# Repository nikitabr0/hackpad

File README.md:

# nikitabr0's hackpad

[Demo video](https://youtu.be/7ATBC-yoFk0)

<table>
  <tr>
    <td>
    <td>
  </tr>
  <tr>
    <td>
    <td>
  </tr>
</table>   

My hackpad features 9 MX-style keyswitches and two EC11 rotary encoders. It has two modes: media control and gaming mode, the latter being mostly for simulators, that require large amounts of keybinds.

In media control mode the keys can be used for pausing, resuming and switching between audiotracks, as well as for using the calcuator (+, -, *, / and =), while the rotary encoders allow for audio volume and screen brightness control, with their switches set to muting audio and locking the screen.

In gaming mode all switches (including those of EC11s) register as F13-F22 presses, with the rotary encoders triggering Right CTRL + F13/14/15/16 on rotation. These keycodes were choosed as they are not included on most keyboards and thus largely unused.

The firmware if written in KMK for the sake of simplicity, although I may try rewriting it in QMK one day. The CAD was done in FreeCAD.

#

### Schematic

### PCB layout

### Case assembly

#

## Bill of materials:
- 1x Seeed XIAO RP2040 DIP
- 9x MX-style switches
- 2x EC11 rotary encoders
- 9x Blank DSA keycaps
- 11x Through-hole 1N4148 diodes
- 4x M3x5mx4mm heatset inserts

I will be printing the case by myself and as I already have some mounting hardware, I will be using it in this project:
- 4x M3x12 SHCS
- 3x M3x8 SHCS

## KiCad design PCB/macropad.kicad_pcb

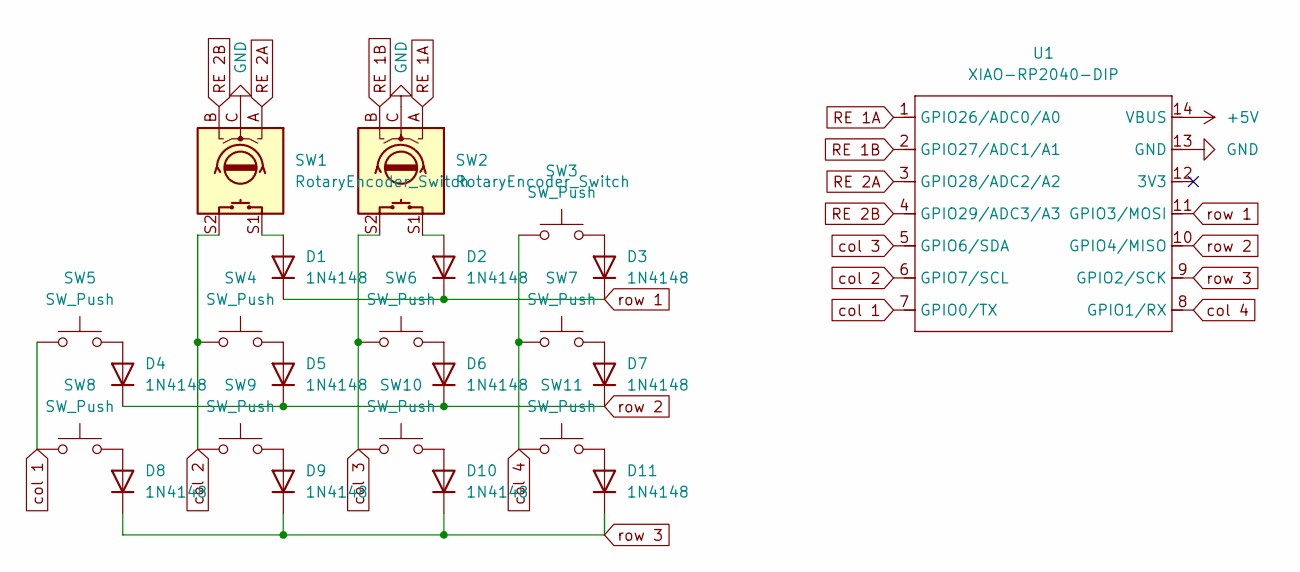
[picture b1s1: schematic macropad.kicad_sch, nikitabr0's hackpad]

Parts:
D1, D2, D3, D4, D5, D6, D7, D8, D9, D10, D11: 1N4148; D_DO-35_SOD27_P7.62mm_Horizontal
SW1, SW2: RotaryEncoder_Switch; RotaryEncoder_Alps_EC11E-Switch_Vertical_H20mm
SW3, SW4, SW5, SW6, SW7, SW8, SW9, SW10, SW11: SW_Push; SW_Cherry_MX_PCB_1.00u
U1: XIAO-RP2040-DIP

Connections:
+5V: U1.14 (VBUS)
GND: SW1.C, SW2.C, U1.13 (GND)
unnamed: D1.2 (A), SW1.S1
unnamed: D2.2 (A), SW2.S1
unnamed: D3.2 (A), SW3.2
unnamed: D4.2 (A), SW5.2
unnamed: D5.2 (A), SW4.2
unnamed: D6.2 (A), SW6.2
unnamed: D7.2 (A), SW7.2
unnamed: D8.2 (A), SW8.2
unnamed: D9.2 (A), SW9.2
unnamed: D10.2 (A), SW10.2
unnamed: D11.2 (A), SW11.2
RE 1A: SW2.A, U1.1 (GPIO26/ADC0/A0)
RE 1B: SW2.B, U1.2 (GPIO27/ADC1/A1)
RE 2A: SW1.A, U1.3 (GPIO28/ADC2/A2)
RE 2B: SW1.B, U1.4 (GPIO29/ADC3/A3)
col 1: SW5.1, SW8.1, U1.7 (GPIO0/TX)
col 2: SW1.S2, SW4.1, SW9.1, U1.6 (GPIO7/SCL)
col 3: SW2.S2, SW6.1, SW10.1, U1.5 (GPIO6/SDA)
col 4: SW3.1, SW7.1, SW11.1, U1.8 (GPIO1/RX)
row 1: D1.1 (K), D2.1 (K), D3.1 (K), U1.11 (GPIO3/MOSI)
row 2: D4.1 (K), D5.1 (K), D6.1 (K), D7.1 (K), U1.10 (GPIO4/MISO)
row 3: D8.1 (K), D9.1 (K), D10.1 (K), D11.1 (K), U1.9 (GPIO2/SCK)

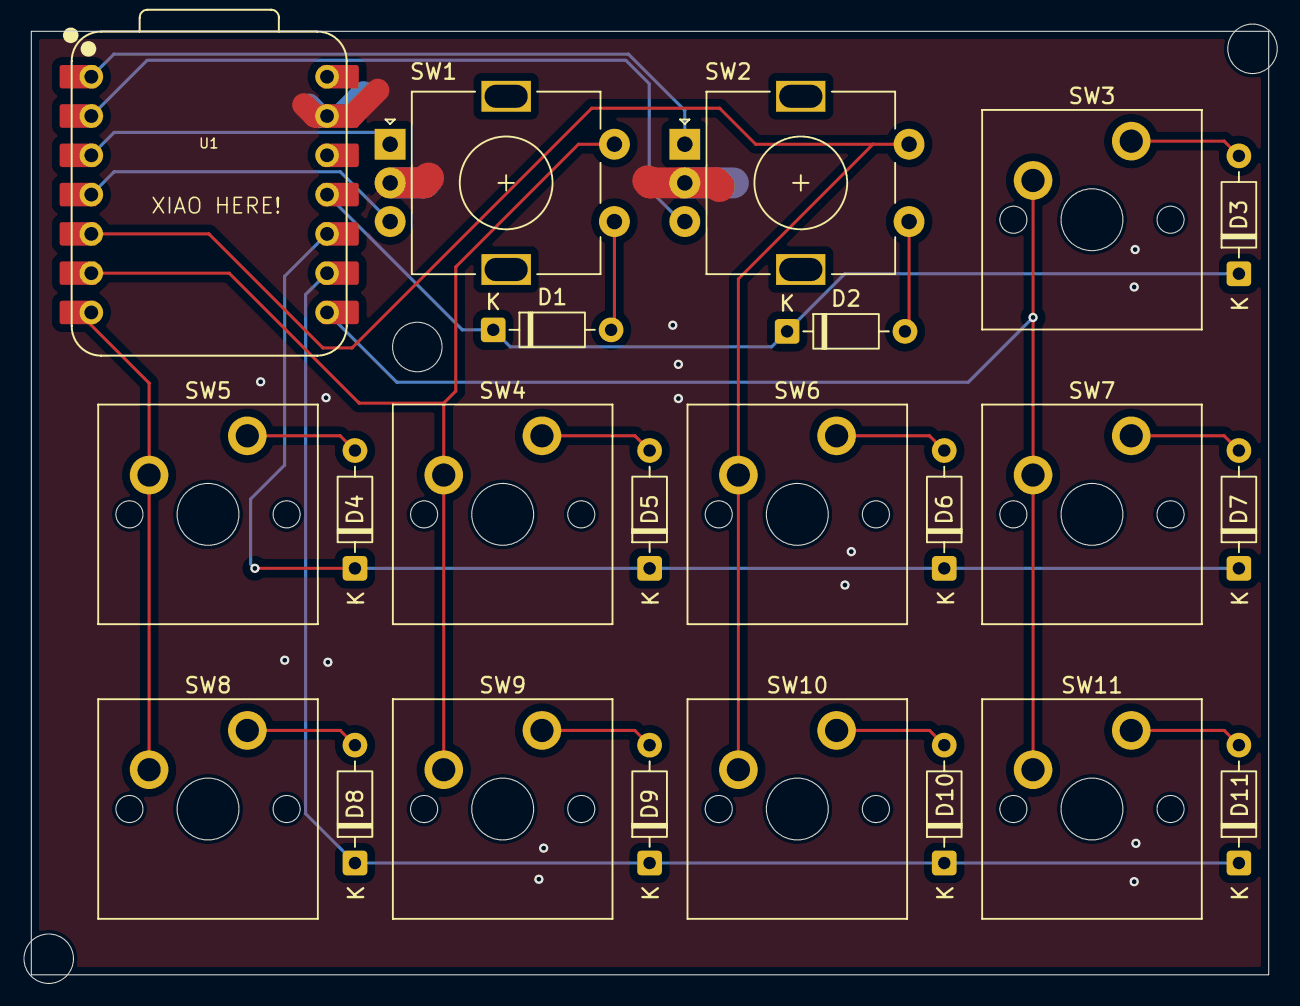
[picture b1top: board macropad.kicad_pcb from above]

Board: 2 copper layers, 80.0 x 61.0 mm, 23 parts (0 on the bottom side), 23 nets.

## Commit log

2025-11-30 Added PCB and CAD files
2025-12-01 Added knobs for rotary encoders and KMK firmware
2025-12-01 Fixed ground fill on the PCB
2026-01-22 Firmware fixes
2026-01-22 Added finished hackpad images
